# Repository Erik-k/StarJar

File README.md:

# StarJar
Radiation controlled Christmas lights.

For pictures and a thorough write-up, visit http://knek-tek.me/index.php/2018/01/09/radiation-controlled-christmas-lights/

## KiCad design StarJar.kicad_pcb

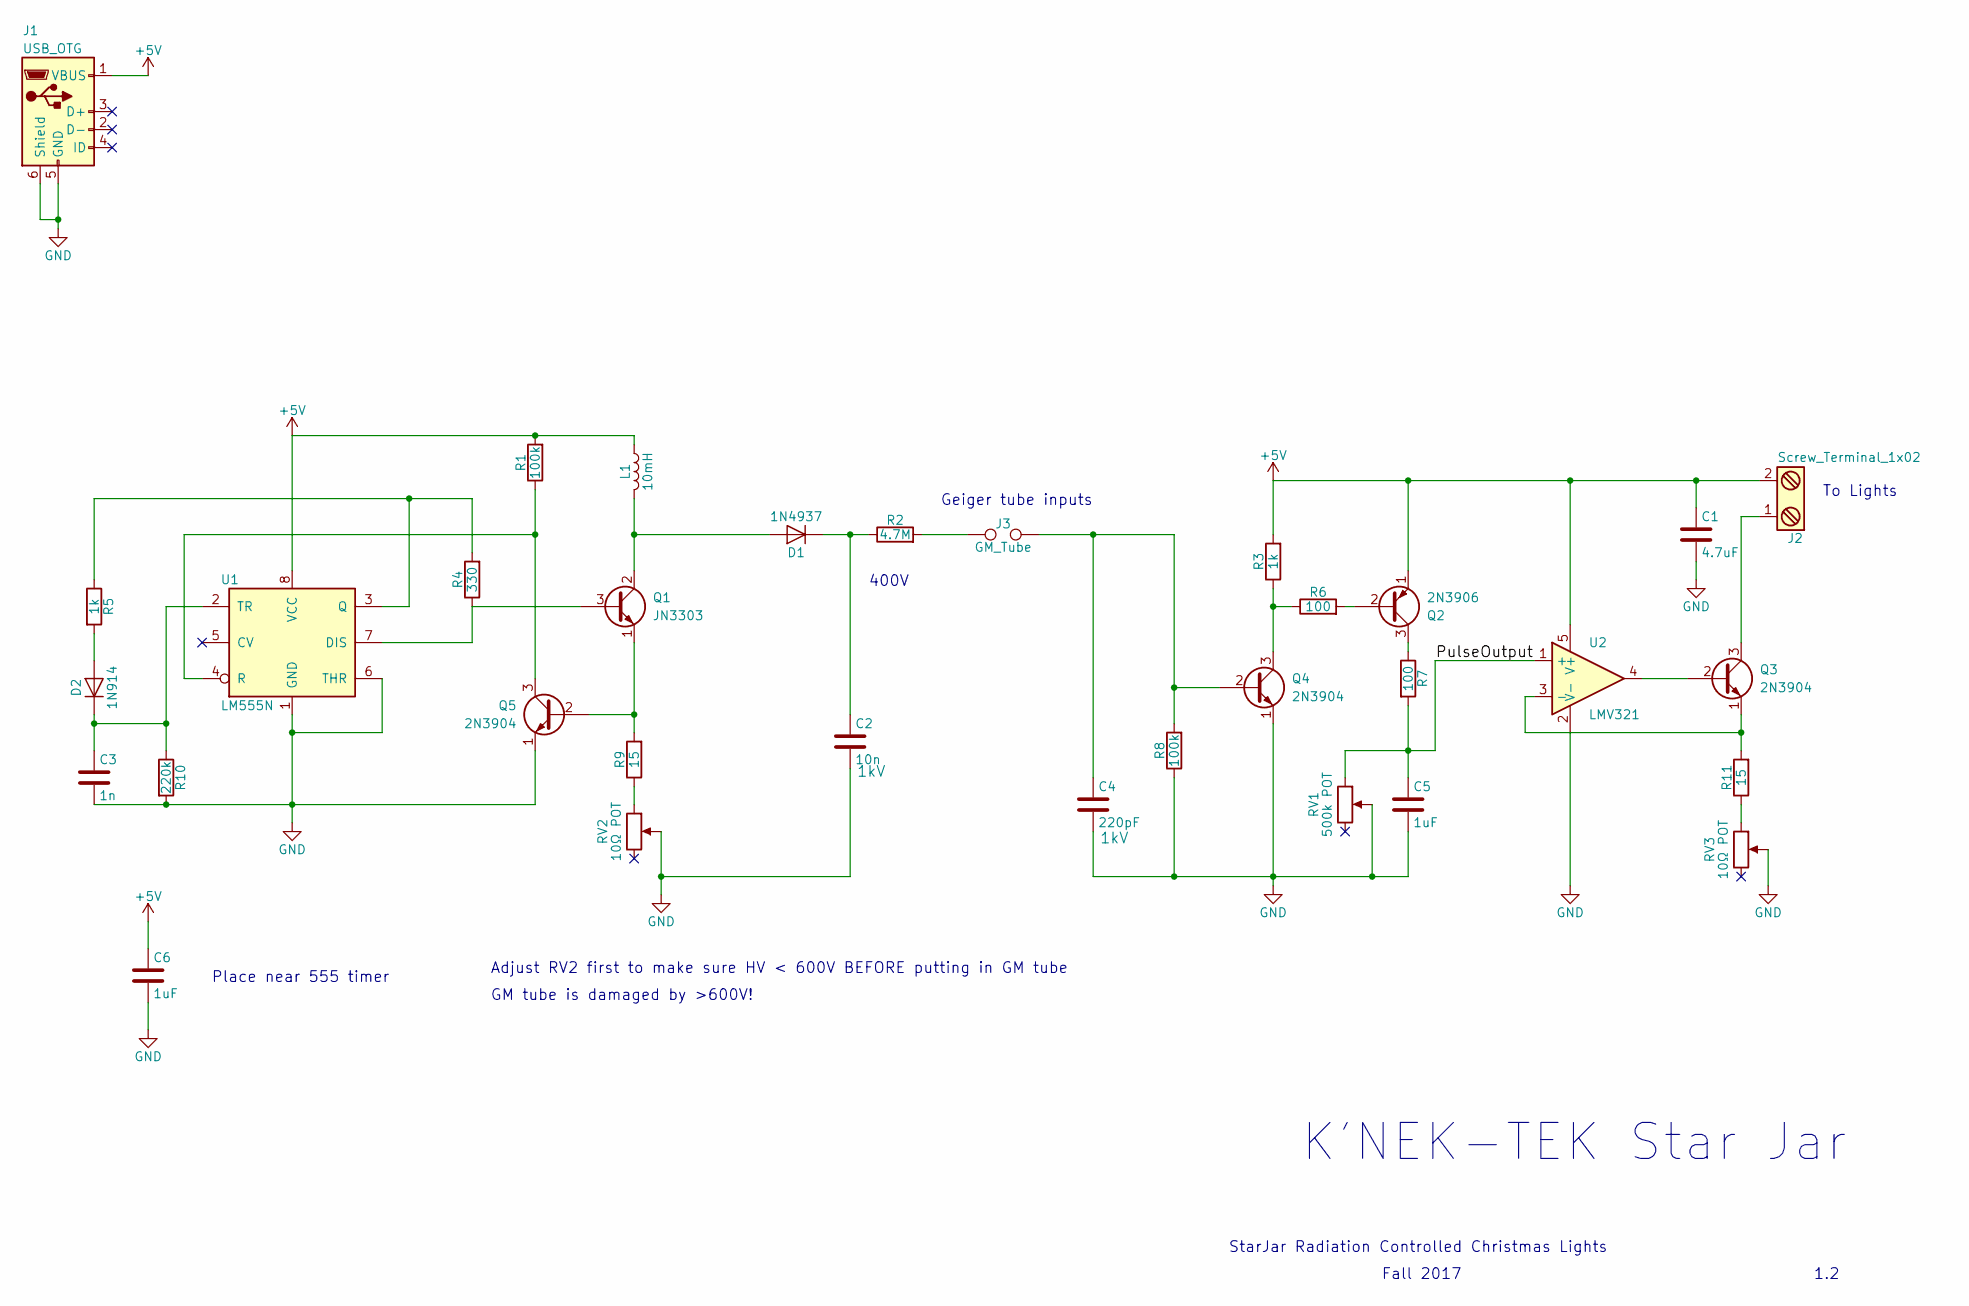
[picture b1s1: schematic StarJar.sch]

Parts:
C1: 4.7uF; C_1210_HandSoldering
C2: 10n; C_1210_HandSoldering; Voltage 1kV
C3: 1n; C_1210_HandSoldering
C4: 220pF; C_1210_HandSoldering; Voltage 1kV
C5, C6: 1uF; C_1210_HandSoldering
D1: 1N4937; D_DO-41_SOD81_P12.70mm_Horizontal
D2: 1N914; D_DO-41_SOD81_P12.70mm_Horizontal
J1: USB_OTG; USB_Micro-B_big_holes_for_OSHpark
J2: Screw_Terminal_1x02; TerminalBlock_Pheonix_MKDS1.5-2pol
J3: GM_Tube; WireConnection_1.50mmDrill
L1: 10mH; R_Axial_DIN0411_L9.9mm_D3.6mm_P7.62mm_Vertical
Q1: JN3303; TO-92_Inline_Wide
Q2: 2N3906; TO-92_Inline_Wide
Q3, Q4, Q5: 2N3904; TO-92_Inline_Wide
R1, R8: 100k; R_Axial_DIN0411_L9.9mm_D3.6mm_P5.08mm_Vertical
R2: 4.7M; R_Axial_DIN0411_L9.9mm_D3.6mm_P5.08mm_Vertical
R3, R5: 1k; R_Axial_DIN0411_L9.9mm_D3.6mm_P5.08mm_Vertical
R4: 330; R_Axial_DIN0411_L9.9mm_D3.6mm_P5.08mm_Vertical
R6, R7: 100; R_Axial_DIN0411_L9.9mm_D3.6mm_P5.08mm_Vertical
R9, R11: 15; R_Axial_DIN0411_L9.9mm_D3.6mm_P5.08mm_Vertical
R10: 220k; R_Axial_DIN0411_L9.9mm_D3.6mm_P5.08mm_Vertical
RV1: 500k POT; Potentiometer_Trimmer_Suntan_TSR-3386P_Horizontal
RV2, RV3: 10Ω POT; Potentiometer_Trimmer_Suntan_TSR-3386P_Horizontal
U1: LM555N; DIP-8_W7.62mm_Socket
U2: LMV321; SOT-23-5_HandSoldering

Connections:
+5V: C1.1, C6.1, J1.1 (VBUS), J2.2, L1.1, Q2.1 (E), R1.2, R3.2, U1.8 (VCC), U2.5 (V+)
/PulseOutput: C5.1, R7.2, RV1.1, U2.1 (+)
GND: C1.2, C2.2, C3.2, C4.2, C5.2, C6.2, J1.5 (GND), J1.6 (Shield), Q4.1 (E), Q5.1 (E), R8.1, R10.2, RV1.2, RV2.2, RV3.2, U1.1 (GND), U1.6 (THR), U2.2 (V-)
unnamed: C2.1, D1.1 (K), R2.1
unnamed: C3.1, D2.1 (K), R10.1, U1.2 (TR)
unnamed: C4.1, J3.2, Q4.2 (B), R8.2
unnamed: D1.2 (A), L1.2, Q1.2 (C)
unnamed: D2.2 (A), R5.2
unnamed: J2.1, Q3.3 (C)
unnamed: J3.1, R2.2
unnamed: Q1.1 (E), Q5.2 (B), R9.2
unnamed: Q1.3 (B), R4.1, U1.7 (DIS)
unnamed: Q2.2 (B), R6.2
unnamed: Q2.3 (C), R7.1
unnamed: Q3.1 (E), R11.2, U2.3 (-)
unnamed: Q3.2 (B), U2.4
unnamed: Q4.3 (C), R3.1, R6.1
unnamed: Q5.3 (C), R1.1, U1.4 (R)
unnamed: R4.2, R5.1, U1.3 (Q)
unnamed: R9.1, RV2.1
unnamed: R11.1, RV3.1

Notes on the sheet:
StarJar Radiation Controlled Christmas Lights
Fall 2017
1.2
Geiger tube inputs
400V
To Lights
Place near 555 timer
Adjust RV2 first to make sure HV < 600V BEFORE putting in GM tube
GM tube is damaged by >600V!
K'NEK-TEK Star Jar

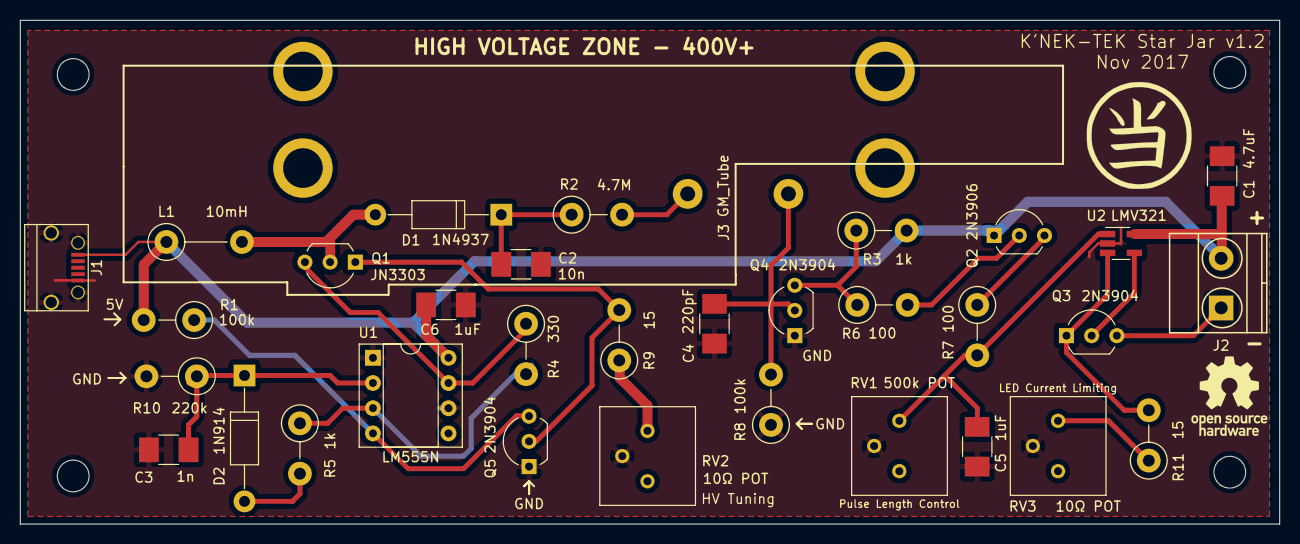
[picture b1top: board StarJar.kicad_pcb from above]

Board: 2 copper layers, 127.0 x 50.8 mm, 35 parts (0 on the bottom side), 21 nets.

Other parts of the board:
FuseHolder1, FuseHolder1#2: ZipTie; GM_tube_ziptie_mounts

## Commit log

2017-10-17 FirstUpload
    First upload at v1.1. v1.0 not on Github, but I produced the PCBs, populated and tested one, and realized fixes and changes that needed to be made. Specifically the opamp and BJT to do voltage-contro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
2017-10-18 Add files via upload
    v1.1 routing done and ready to order
2017-10-27 Add files via upload
    PCB ordered from OSH Park. I realized I should use zip ties rather than fuse holders for the SBM-20/U GM tube.
2017-11-17 Add files via upload
    v1.2 board layout finished, ready to order. Changes: zip tie mounts for GM tube, USB micro-B rather than USB-A, added new components to fix pulse size issue.
2017-11-18 Add files via upload
    Minor changes to PCB silkscreen. Ordered the boards.
2017-12-01 Final BOM.
